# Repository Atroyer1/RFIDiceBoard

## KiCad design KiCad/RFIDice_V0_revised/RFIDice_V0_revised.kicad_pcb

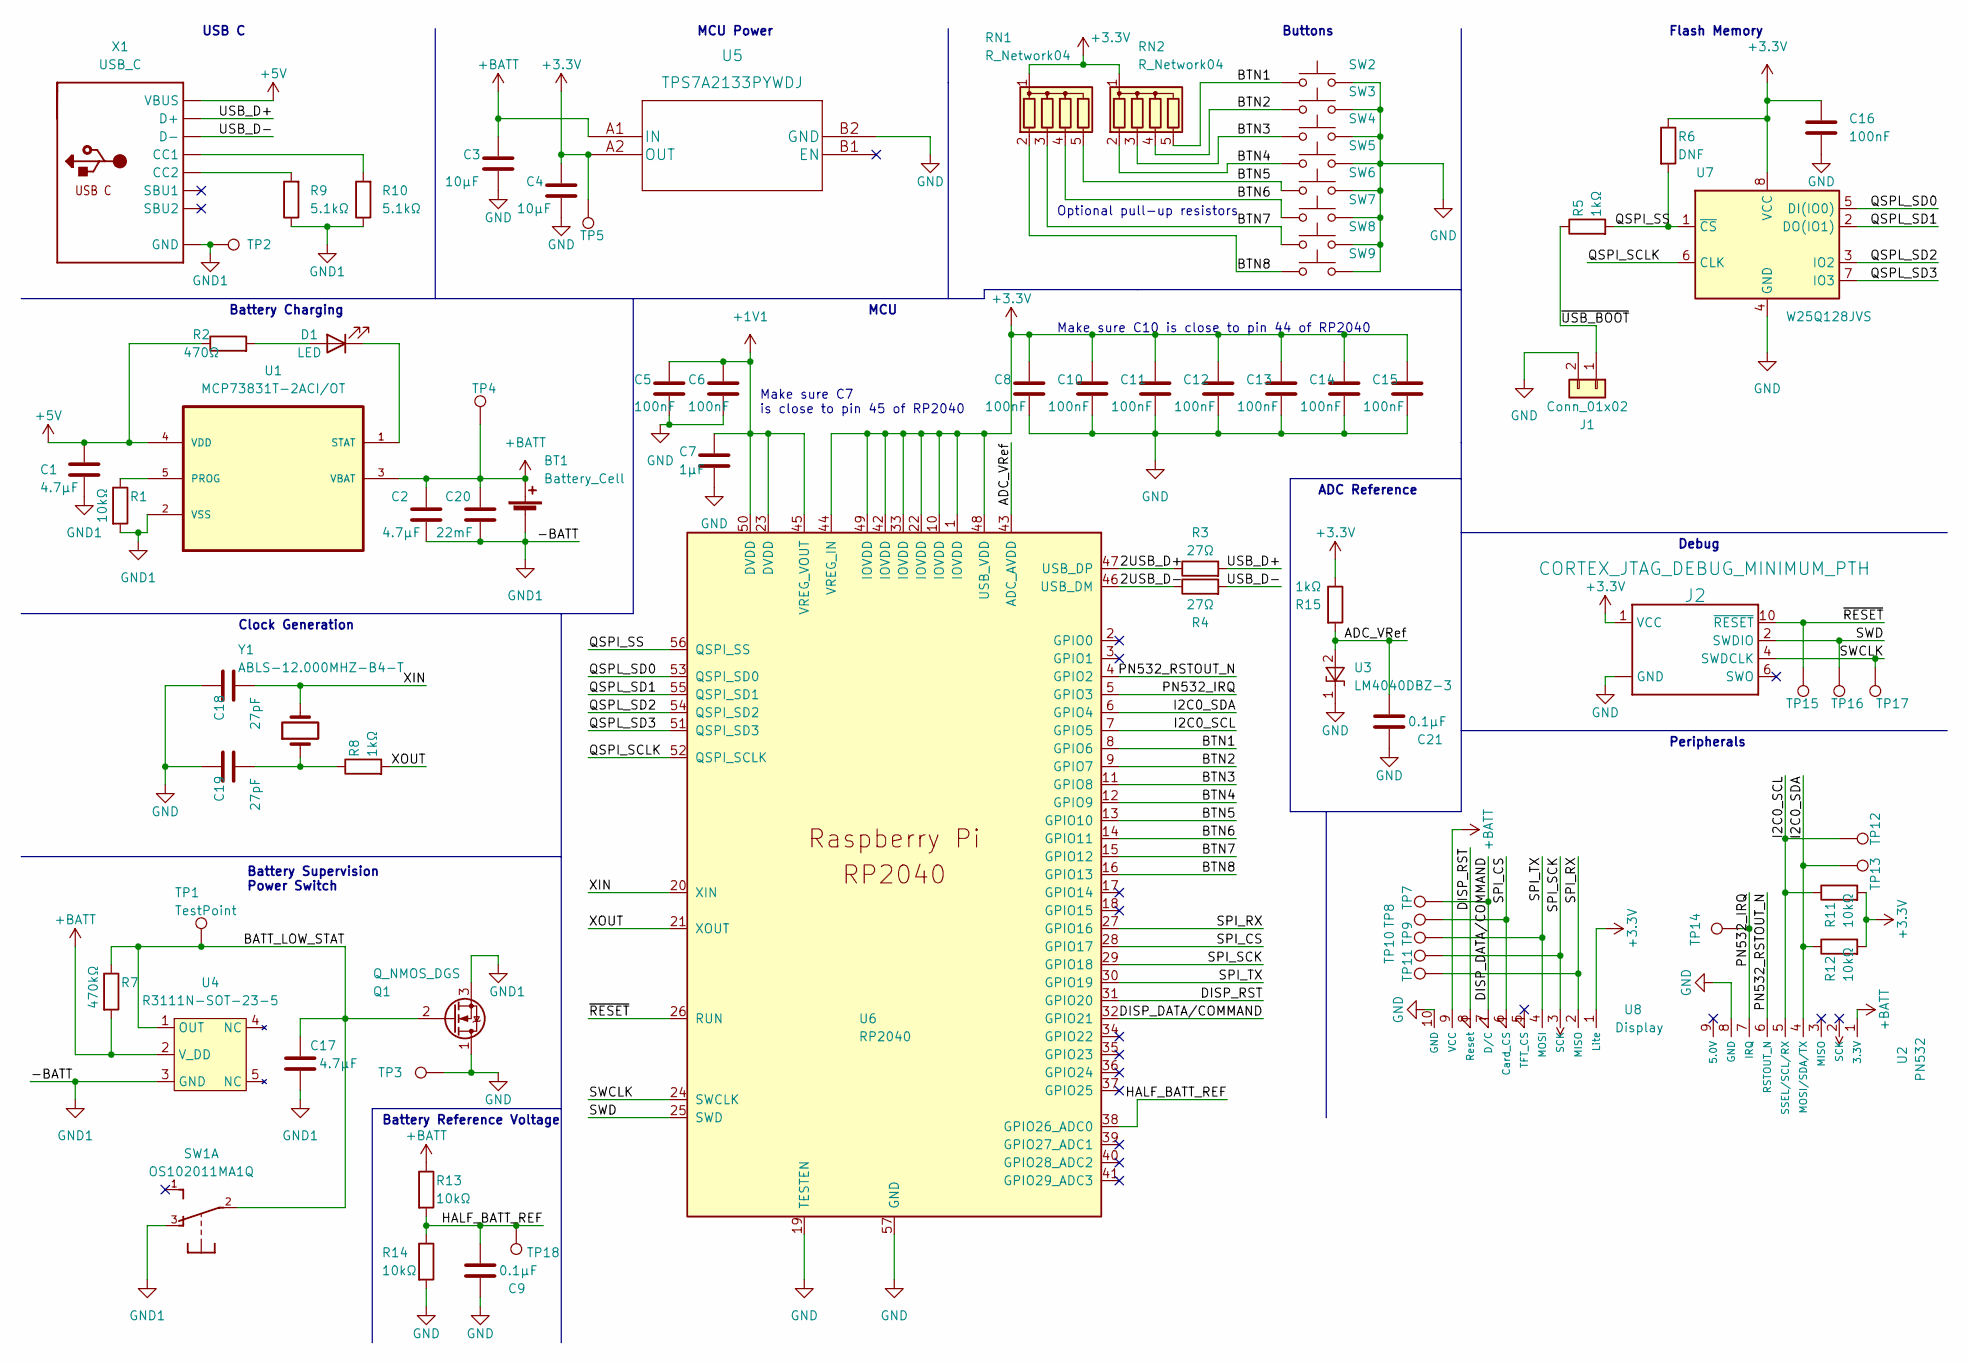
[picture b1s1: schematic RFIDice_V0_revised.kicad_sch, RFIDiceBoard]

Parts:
BT1: Battery_Cell; AndyBattery
C1, C2, C17: 4.7µF; C_0603_1608Metric_Pad1.08x0.95mm_HandSolder
C3, C4: 10µF; C_0603_1608Metric_Pad1.08x0.95mm_HandSolder
C5, C6, C8, C10, C11, C12, C13, C14, C15, C16: 100nF; C_0603_1608Metric_Pad1.08x0.95mm_HandSolder
C7: 1µF; C_0603_1608Metric_Pad1.08x0.95mm_HandSolder
C9, C21: 0.1µF; C_0603_1608Metric_Pad1.08x0.95mm_HandSolder
C18, C19: 27pF; C_0603_1608Metric_Pad1.08x0.95mm_HandSolder
C20: 22mF; CP_EIA-3528-21_Kemet-B_Pad1.50x2.35mm_HandSolder
D1: LED; LED_0603_1608Metric_Pad1.05x0.95mm_HandSolder
J1: Conn_01x02; PinHeader_1x02_P2.54mm_Vertical
J2: CORTEX_JTAG_DEBUG_MINIMUM_PTH; 2X5-PTH-1.27MM
Q1: Q_NMOS_DGS; SOT-23
R1, R11, R12, R13, R14: 10kΩ; R_0603_1608Metric_Pad0.98x0.95mm_HandSolder
R2: 470Ω; R_0603_1608Metric_Pad0.98x0.95mm_HandSolder
R3, R4: 27Ω; R_0603_1608Metric_Pad0.98x0.95mm_HandSolder
R5, R8, R15: 1kΩ; R_0603_1608Metric_Pad0.98x0.95mm_HandSolder
R6: DNF; R_0603_1608Metric_Pad0.98x0.95mm_HandSolder
R7: 470kΩ; R_0603_1608Metric_Pad0.98x0.95mm_HandSolder
R9, R10: 5.1kΩ; R_0603_1608Metric_Pad0.98x0.95mm_HandSolder
RN1, RN2: R_Network04; R_Array_Convex_4x1206
SW1: OS102011MA1Q
SW2, SW3, SW4, SW5, SW6, SW7, SW8, SW9: SW_Push; EVP-ASDC1A_Tactile_PushButton
TP1, TP2, TP3, TP4, TP5, TP7, TP8, TP9, TP10, TP11, TP12, TP13, TP14, TP15, TP16, TP17, TP18: TestPoint; TestPoint_Keystone_5000-5004_Miniature
U1: MCP73831T-2ACI/OT; SOT-23-5_HandSoldering; MPN MCP73831T-2ACI/OT
U2: PN532; ThroughHolePN532BrkOutBoardMount
U3: LM4040DBZ-3; SOT-23
U4: R3111N-SOT-23-5; SOT-23-5_HandSoldering
U5: TPS7A2133PYWDJ
U6: RP2040; RP2040-QFN-56
U7: W25Q128JVS; SOIC-8_5.23x5.23mm_P1.27mm
U8: Display; ThroughHoldDisplayMount
X1: USB_C; USB_C_CUSB31-CFM2AX-01-X_copy
Y1: ABLS-12.000MHZ-B4-T; Crystal_SMD_HC49-US

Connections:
+1V1: C5.1, C6.1, C7.1, U6.23 (DVDD), U6.45 (VREG_VOUT), U6.50 (DVDD)
+3V3: C4.1, C8.1, C10.1, C11.1, C12.1, C13.1, C14.1, C15.1, C16.1, J2.1 (VCC), R6.1, R11.2, R12.2, R15.1, RN1.1 (common), RN2.1 (common), TP5.1, U5.A2 (OUT), U6.1 (IOVDD), U6.10 (IOVDD), U6.22 (IOVDD), U6.33 (IOVDD), U6.42 (IOVDD), U6.44 (VREG_IN), U6.48 (USB_VDD), U6.49 (IOVDD), U7.8 (VCC), U8.1 (Lite)
+5V: C1.1, R2.1, U1.4 (VDD), X1.A4B9 (VBUS), X1.B4A9 (VBUS)
+BATT: BT1.1 (+), C2.1, C3.1, C20.1, R7.2, R13.1, TP4.1, U1.3 (VBAT), U2.1 (3.3V), U4.2 (V_DD), U5.A1 (IN), U8.9 (VCC)
/2USB_D+: R3.1, U6.47 (USB_DP)
/2USB_D-: R4.1, U6.46 (USB_DM)
/ADC_VRef: C21.1, R15.2, U3.2 (A), U6.43 (ADC_AVDD)
/BATT_LOW_STAT: C17.1, Q1.2 (G), R7.1, SW1.2, TP1.1, U4.1 (OUT)
/BTN1: RN2.5 (R4), SW2.1, U6.8 (GPIO6)
/BTN2: RN2.4 (R3), SW3.1, U6.9 (GPIO7)
/BTN3: RN2.3 (R2), SW4.1, U6.11 (GPIO8)
/BTN4: RN2.2 (R1), SW5.1, U6.12 (GPIO9)
/BTN5: RN1.5 (R4), SW6.1, U6.13 (GPIO10)
/BTN6: RN1.4 (R3), SW7.1, U6.14 (GPIO11)
/BTN7: RN1.3 (R2), SW8.1, U6.15 (GPIO12)
/BTN8: RN1.2 (R1), SW9.1, U6.16 (GPIO13)
/DISP_DATA/COMMAND: TP7.1, U6.32 (GPIO21), U8.7 (D/C)
/DISP_RST: U6.31 (GPIO20), U8.8 (Reset)
/HALF_BATT_REF: C9.1, R13.2, R14.1, TP18.1, U6.38 (GPIO26_ADC0)
/I2C0_SCL: R11.1, TP12.1, U2.5 (SSEL/SCL/RX), U6.7 (GPIO5)
/I2C0_SDA: R12.1, TP13.1, U2.4 (MOSI/SDA/TX), U6.6 (GPIO4)
/PN532_IRQ: TP14.1, U2.7 (IRQ), U6.5 (GPIO3)
/PN532_RSTOUT_N: U2.6 (RSTOUT_N), U6.4 (GPIO2)
/QSPI_SCLK: U6.52 (QSPI_SCLK), U7.6 (CLK)
/QSPI_SS: R5.2, R6.2, U6.56 (QSPI_SS), U7.1 (~CS)
/QSPL_SD0: U6.53 (QSPI_SD0), U7.5 (DI(IO0))
/QSPL_SD1: U6.55 (QSPI_SD1), U7.2 (DO(IO1))
/QSPL_SD2: U6.54 (QSPI_SD2), U7.3 (IO2)
/QSPL_SD3: U6.51 (QSPI_SD3), U7.7 (IO3)
/SPI_CS: TP8.1, U6.28 (GPIO17), U8.6 (Card_CS)
/SPI_RX: TP11.1, U6.27 (GPIO16), U8.2 (MISO)
/SPI_SCK: TP10.1, U6.29 (GPIO18), U8.3 (SCK)
/SPI_TX: TP9.1, U6.30 (GPIO19), U8.4 (MOSI)
/SWCLK: J2.4 (SWDCLK), TP17.1, U6.24 (SWCLK)
/SWD: J2.2 (SWDIO), TP16.1, U6.25 (SWD)
/USB_D+: R3.2, X1.A6 (D+), X1.B6 (D+)
/USB_D-: R4.2, X1.A7 (D-), X1.B7 (D-)
/XIN: C18.2, U6.20 (XIN), Y1.2
/XOUT: R8.2, U6.21 (XOUT)
/~RESET: J2.10 (~RESET), TP15.1, U6.26 (RUN)
/~USB_BOOT: J1.1, R5.1
GND: C3.2, C4.2, C5.2, C6.2, C7.2, C8.2, C9.2, C10.2, C11.2, C12.2, C13.2, C14.2, C15.2, C16.2, C18.1, C19.1, C21.2, J1.2, J2.3 (GND), J2.5 (GND), J2.9 (GND), Q1.1 (D), R14.2, SW2.2, SW3.2, SW4.2, SW5.2, SW6.2, SW7.2, SW8.2, SW9.2, TP3.1, U2.8 (GND), U3.1 (K), U5.B2 (GND), U6.19 (TESTEN), U6.57 (GND), U7.4 (GND), U8.10 (GND)
GND1: BT1.2 (-), C1.2, C2.2, C17.2, C20.2, Q1.3 (S), R1.2, R9.1, R10.1, SW1.3, TP2.1, U1.2 (VSS), U4.3 (GND), X1.A1B12 (GND), X1.B1A12 (GND)
unnamed: C19.2, R8.1, Y1.1
unnamed: D1.1 (K), U1.1 (STAT)
unnamed: D1.2 (A), R2.2
unnamed: R1.1, U1.5 (PROG)
unnamed: R9.2, X1.B5 (CC2)
unnamed: R10.2, X1.A5 (CC1)

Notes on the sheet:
ADC Reference
USB C
Battery Reference Voltage
Debug
Flash Memory
Battery Charging
Battery Supervision Power Switch
MCU
Make sure C7 is close to pin 45 of RP2040
Clock Generation
Make sure C10 is close to pin 44 of RP2040
MCU Power
Optional pull-up resistors
Peripherals
Buttons

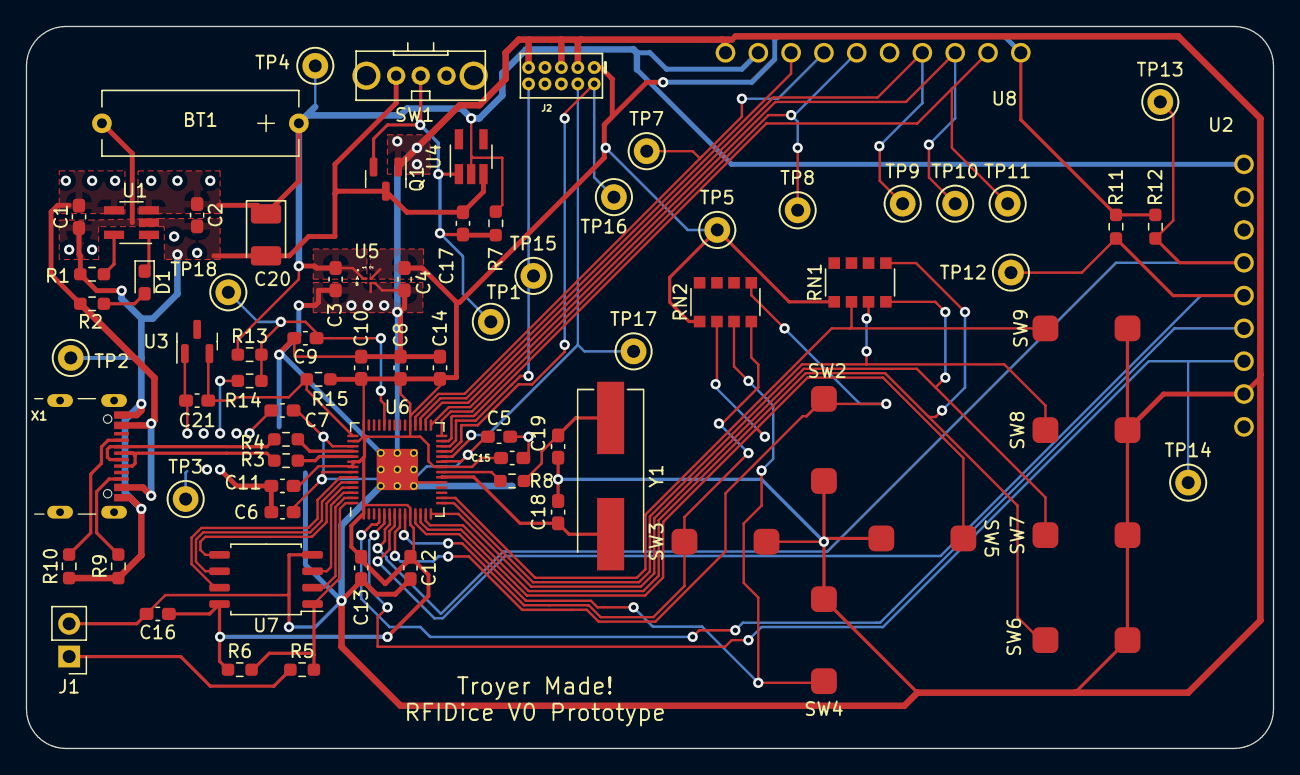
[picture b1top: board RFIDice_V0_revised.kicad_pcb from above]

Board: 2 copper layers, 96.5 x 55.9 mm, 79 parts (0 on the bottom side), 49 nets.

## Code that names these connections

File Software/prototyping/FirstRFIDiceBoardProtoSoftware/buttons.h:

#define BTN1_PIN 6
#define BTN2_PIN 7
#define BTN3_PIN 8
#define BTN4_PIN 9
#define BTN5_PIN 10
#define BTN6_PIN 11
#define BTN7_PIN 12
#define BTN8_PIN 13

void button_init(void);

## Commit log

2022-09-20 first commit x5
2022-09-20 Added documentation and KiCad
2022-09-20 Color change display prototyping
2022-09-20 Playing with Proto display
2022-09-20 Added final winter quarter submission
2022-09-20 x-direction defined in main test functions
2022-10-11 display prototyping continued. troyermade folder added
2022-10-16 Display proto has letter A support
2022-10-17 Pixel letters and numbers added to protototype code
2022-10-19 troyermade folder contains a clean start with a display init for the final software prototype
2022-10-26 troyermade tftdisplay looking nicer
2022-10-27 bus_scan added to prototype
2022-10-30 PN532 prototyping in progress
2022-10-31 Test code for tft display string drawing works
2022-11-07 Buttons kinda work
2022-11-08 getFirmwareVersion prototype working
2022-11-16 Possible hardware issue
2022-11-17 Added delays and hardware maybe issue went away
2022-11-23 Rand_gen test now displays seconds to display
2022-11-29 Random number generator is operational
2022-11-30 adc test ready
2022-12-01 adc working. All things working. Time for OSing
2022-12-05 Final software template created
2022-12-08 Trying and failing to get systickdelay moving
2022-12-09 Move stuff around for organization
2022-12-17 reorganized and got a timer working for adc irq
2022-12-19 Battery display prototype working
2022-12-19 Hysteresis added to battery display
2022-12-22 Moving COmputers woops commit
2022-12-23 Buttons debounced by automagic hysteresis on the RP2040
2022-12-29 Bones for tftdisplay added
2022-12-31 Buttons didn't work as planned. Got a cooperative loop going though
2023-01-03 Timer delay working, button 1 working
2023-01-05 First time an RFID tag has generated random numbers
2023-01-10 V01 complete. Have to start testing
2023-01-12 Software implementation finished. Cleanup is next
2023-01-16 Code prettied up for human consumption
2023-01-25 Testing code added and removed
2023-03-03 Added V1 Software directory with new idle animation and bigger chars
2023-03-03 Added buttons to the screen
2023-03-09 Hopefully this works I need to go to the lab
2023-03-14 Changing systems. Forgot what I changed
2023-03-17 Software v1.0
